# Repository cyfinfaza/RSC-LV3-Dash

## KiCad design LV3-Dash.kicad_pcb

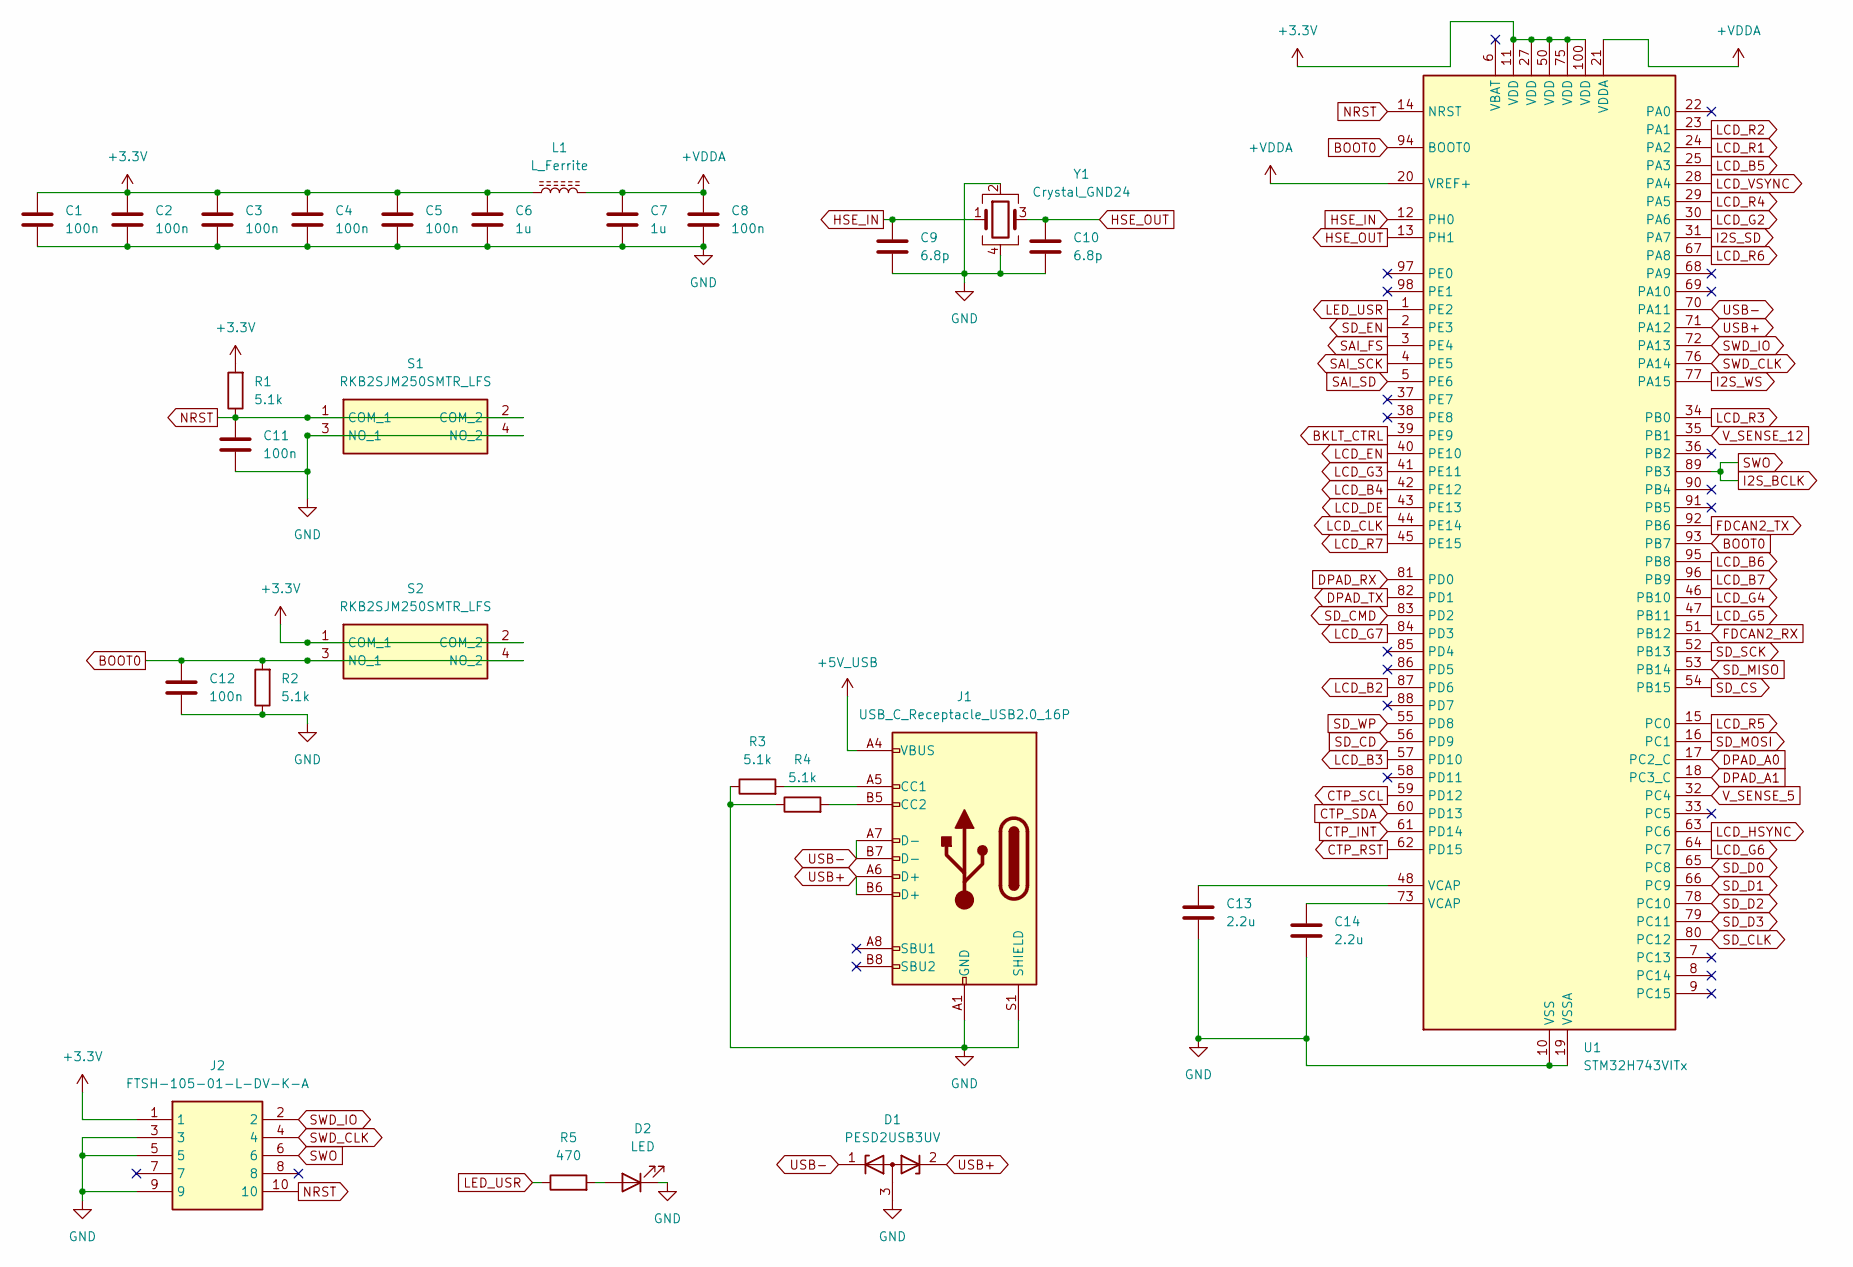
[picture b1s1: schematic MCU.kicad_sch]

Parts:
C1, C2, C3, C4, C5, C8, C11, C12: 100n; C_0603_1608Metric_Pad1.08x0.95mm_HandSolder
C6, C7: 1u; C_0603_1608Metric_Pad1.08x0.95mm_HandSolder
C9, C10: 6.8p; C_0603_1608Metric_Pad1.08x0.95mm_HandSolder
C13, C14: 2.2u; C_0603_1608Metric_Pad1.08x0.95mm_HandSolder
D1: PESD2USB3UV; SOT-23W
D2: LED; LED_0603_1608Metric_Pad1.05x0.95mm_HandSolder
J1: USB_C_Receptacle_USB2.0_16P; USB_C_Receptacle_HRO_TYPE-C-31-M-12
J2: FTSH-105-01-L-DV-K-A; FTSH-105-XX-YYY-DV-K-A; Mouser Part Number 200-FTSH10501LDVKA
L1: L_Ferrite; L_0603_1608Metric_Pad1.05x0.95mm_HandSolder
R1, R2, R3, R4: 5.1k; R_0603_1608Metric_Pad0.98x0.95mm_HandSolder
R5: 470; R_0603_1608Metric_Pad0.98x0.95mm_HandSolder
S1, S2: RKB2SJM250SMTR_LFS; RKB2SJM250SMTRLFS; Mouser Part Number 611-RKB2SJM250SMTRLF
U1: STM32H743VITx; LQFP-100_14x14mm_P0.5mm
Y1: Crystal_GND24; Crystal_SMD_3225-4Pin_3.2x2.5mm

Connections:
+3.3V: C1.1, C2.1, C3.1, C4.1, C5.1, C6.1, J2.1, L1.1, R1.2, S2.1 (COM_1), S2.2 (COM_2), U1.11 (VDD), U1.27 (VDD), U1.50 (VDD), U1.75 (VDD), U1.100 (VDD); also elsewhere on the board
+5V_USB: J1.A4 (VBUS), J1.A9 (VBUS), J1.B4 (VBUS), J1.B9 (VBUS); also elsewhere on the board
+VDDA: C7.1, C8.1, L1.2, U1.20 (VREF+), U1.21 (VDDA)
BKLT_CTRL: U1.39 (PE9); also elsewhere on the board
BOOT0: C12.1, R2.2, S2.3 (NO_1), S2.4 (NO_2), U1.93 (PB7), U1.94 (BOOT0)
CTP_INT: U1.61 (PD14); also elsewhere on the board
CTP_RST: U1.62 (PD15); also elsewhere on the board
CTP_SCL: U1.59 (PD12); also elsewhere on the board
CTP_SDA: U1.60 (PD13); also elsewhere on the board
DPAD_A0: U1.17 (PC2_C), U1.82 (PD1); also elsewhere on the board
DPAD_A1: U1.18 (PC3_C), U1.81 (PD0); also elsewhere on the board
FDCAN2_RX: U1.51 (PB12); also elsewhere on the board
FDCAN2_TX: U1.92 (PB6); also elsewhere on the board
GND: C1.2, C2.2, C3.2, C4.2, C5.2, C6.2, C7.2, C8.2, C9.2, C10.2, C11.2, C12.2, C13.2, C14.2, D1.3 (A), D2.1 (K), J1.A1 (GND), J1.A12 (GND), J1.B1 (GND), J1.B12 (GND), J1.S1 (SHIELD), J2.3, J2.5, J2.9, R2.1, R3.1, R4.1, S1.3 (NO_1), S1.4 (NO_2), U1.10 (VSS), U1.19 (VSSA), U1.26 (VSS), U1.49 (VSS), U1.74 (VSS), U1.99 (VSS), Y1.2, Y1.4; also elsewhere on the board
HSE_IN: C9.1, U1.12 (PH0), Y1.1
HSE_OUT: C10.1, U1.13 (PH1), Y1.3
I2S_BCLK: J2.6, U1.89 (PB3); also elsewhere on the board
I2S_SD: U1.31 (PA7); also elsewhere on the board
I2S_WS: U1.77 (PA15); also elsewhere on the board
LCD_B2: U1.87 (PD6); also elsewhere on the board
LCD_B3: U1.57 (PD10); also elsewhere on the board
LCD_B4: U1.42 (PE12); also elsewhere on the board
LCD_B5: U1.25 (PA3); also elsewhere on the board
LCD_B6: U1.95 (PB8); also elsewhere on the board
LCD_B7: U1.96 (PB9); also elsewhere on the board
LCD_CLK: U1.44 (PE14); also elsewhere on the board
LCD_DE: U1.43 (PE13); also elsewhere on the board
LCD_EN: U1.40 (PE10); also elsewhere on the board
LCD_G2: U1.30 (PA6); also elsewhere on the board
LCD_G3: U1.41 (PE11); also elsewhere on the board
LCD_G4: U1.46 (PB10); also elsewhere on the board
LCD_G5: U1.47 (PB11); also elsewhere on the board
LCD_G6: U1.64 (PC7); also elsewhere on the board
LCD_G7: U1.84 (PD3); also elsewhere on the board
LCD_HSYNC: U1.63 (PC6); also elsewhere on the board
LCD_R1: U1.24 (PA2)
LCD_R2: U1.23 (PA1); also elsewhere on the board
LCD_R3: U1.34 (PB0); also elsewhere on the board
LCD_R4: U1.29 (PA5); also elsewhere on the board
LCD_R5: U1.15 (PC0); also elsewhere on the board
LCD_R6: U1.67 (PA8); also elsewhere on the board
LCD_R7: U1.45 (PE15); also elsewhere on the board
LCD_VSYNC: U1.28 (PA4); also elsewhere on the board
LED_USR: R5.1, U1.1 (PE2)
NRST: C11.1, J2.10, R1.1, S1.1 (COM_1), S1.2 (COM_2), U1.14 (NRST)
unnamed: C13.1, U1.48 (VCAP)
unnamed: C14.1, U1.73 (VCAP)
unnamed: D2.2 (A), R5.2
unnamed: J1.A5 (CC1), R3.2
unnamed: J1.B5 (CC2), R4.2
SAI_FS: U1.3 (PE4); also elsewhere on the board
SAI_SCK: U1.4 (PE5); also elsewhere on the board
SAI_SD: U1.5 (PE6); also elsewhere on the board
SD_CD: U1.56 (PD9); also elsewhere on the board
SD_CLK: U1.52 (PB13), U1.80 (PC12); also elsewhere on the board
SD_CMD: U1.16 (PC1), U1.83 (PD2); also elsewhere on the board
SD_CS: U1.54 (PB15), U1.79 (PC11); also elsewhere on the board
SD_D0: U1.53 (PB14), U1.65 (PC8); also elsewhere on the board
SD_D1: U1.66 (PC9); also elsewhere on the board
SD_D2: U1.78 (PC10); also elsewhere on the board
SD_EN: U1.2 (PE3); also elsewhere on the board
SD_WP: U1.55 (PD8); also elsewhere on the board
SWD_CLK: J2.4, U1.76 (PA14)
SWD_IO: J2.2, U1.72 (PA13)
USB+: D1.2 (K), J1.A6 (D+), J1.B6 (D+), U1.71 (PA12)
USB-: D1.1 (K), J1.A7 (D-), J1.B7 (D-), U1.70 (PA11)
V_SENSE_5: U1.32 (PC4); also elsewhere on the board
V_SENSE_12: U1.35 (PB1); also elsewhere on the board

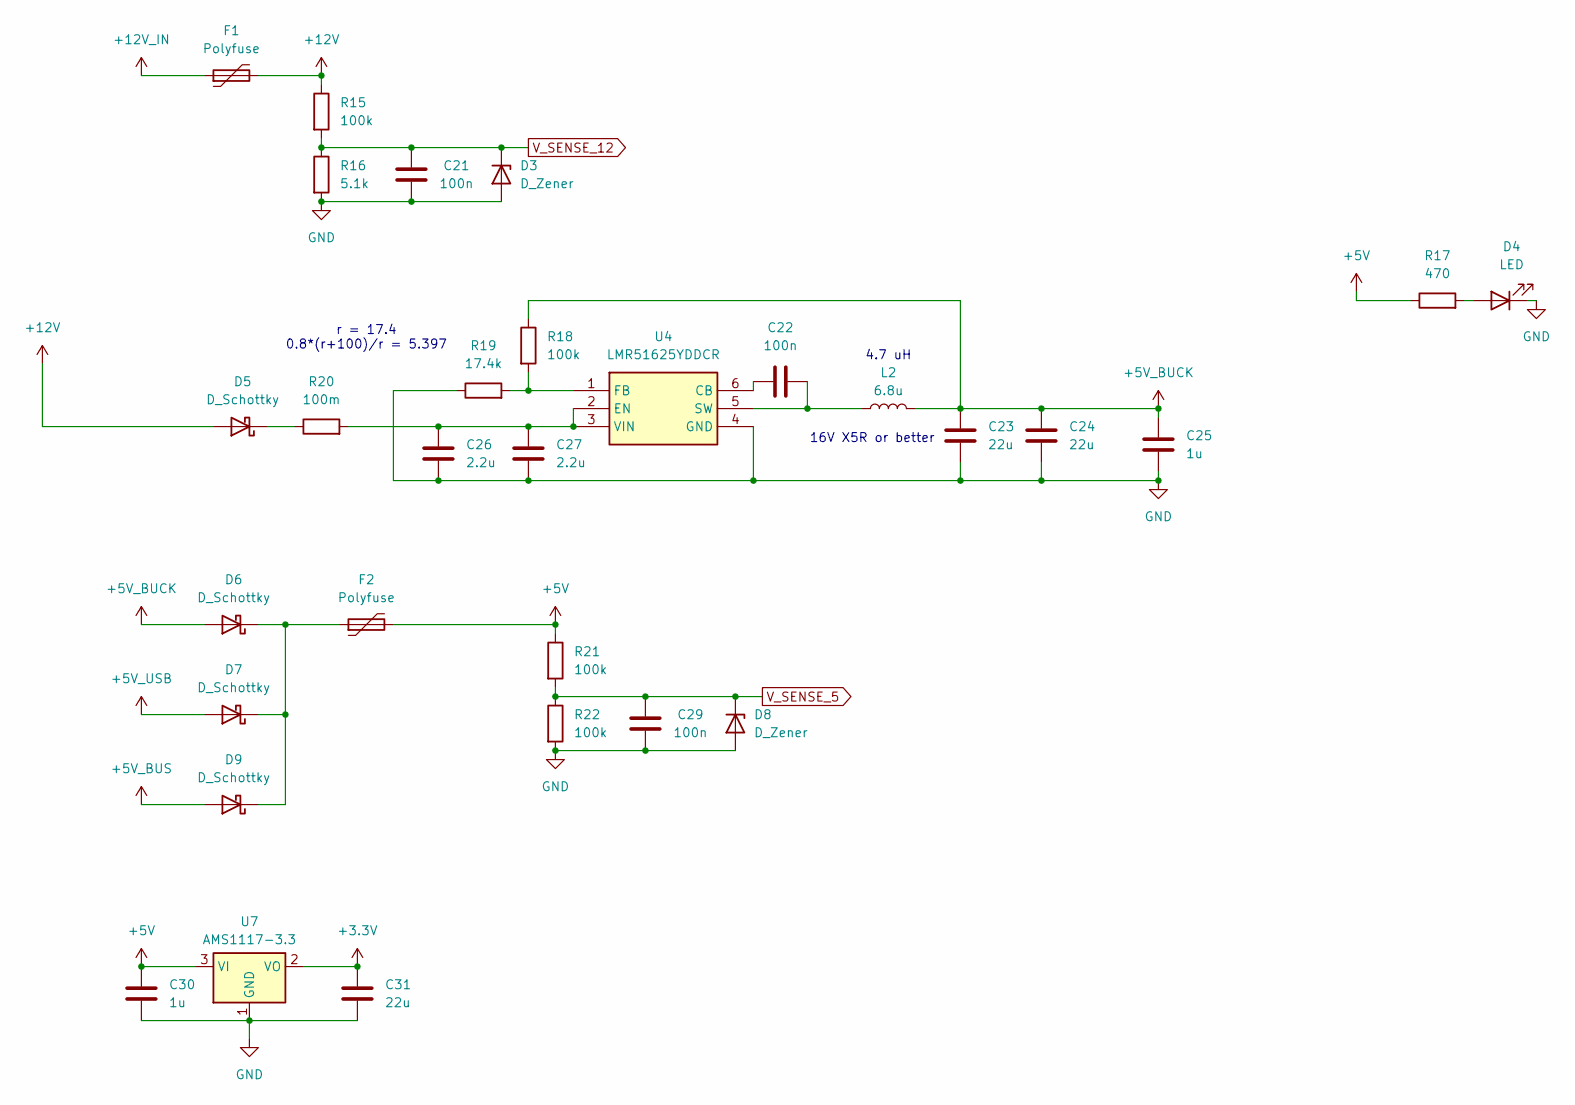
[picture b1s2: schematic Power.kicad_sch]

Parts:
C21, C22, C29: 100n; C_0603_1608Metric_Pad1.08x0.95mm_HandSolder
C23, C24, C31: 22u; C_1206_3216Metric_Pad1.33x1.80mm_HandSolder
C25, C30: 1u; C_0603_1608Metric_Pad1.08x0.95mm_HandSolder
C26, C27: 2.2u; C_0603_1608Metric_Pad1.08x0.95mm_HandSolder
D3, D8: D_Zener; D_SOD-323_HandSoldering
D4: LED; LED_0603_1608Metric_Pad1.05x0.95mm_HandSolder
D5, D6, D7, D9: D_Schottky; D_SOD-123F
F1, F2: Polyfuse; Fuse_1812_4532Metric_Pad1.30x3.40mm_HandSolder
L2: 6.8u; L_Bourns-SRN4018
R15, R18, R21, R22: 100k; R_0603_1608Metric_Pad0.98x0.95mm_HandSolder
R16: 5.1k; R_0603_1608Metric_Pad0.98x0.95mm_HandSolder
R17: 470; R_0603_1608Metric_Pad0.98x0.95mm_HandSolder
R19: 17.4k; R_0603_1608Metric_Pad0.98x0.95mm_HandSolder
R20: 100m; R_1206_3216Metric_Pad1.30x1.75mm_HandSolder
U4: LMR51625YDDCR; SOT95P280X110-6N; Manufacturer_Part_Number LMR51625YFDDCR; Mouser Part Number 595-LMR51625YFDDCR
U7: AMS1117-3.3; SOT-223-3_TabPin2

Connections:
+3.3V: C31.1, U7.2 (VO); also elsewhere on the board
+5V: C30.1, F2.2, R17.1, R21.1, U7.3 (VI); also elsewhere on the board
+5V_BUCK: C23.1, C24.1, C25.1, D6.2 (A), L2.2, R18.1
+5V_BUS: D9.2 (A); also elsewhere on the board
+5V_USB: D7.2 (A); also elsewhere on the board
+12V: D5.2 (A), F1.2, R15.1
+12V_IN: F1.1; also elsewhere on the board
GND: C21.2, C23.2, C24.2, C25.2, C26.2, C27.2, C29.2, C30.2, C31.2, D3.2 (A), D4.1 (K), D8.2 (A), R16.2, R19.1, R22.2, U4.4 (GND), U7.1 (GND); also elsewhere on the board
unnamed: D4.2 (A), R17.2
unnamed: D5.1 (K), R20.1
unnamed: D6.1 (K), D7.1 (K), D9.1 (K), F2.1
unnamed: C22.1, U4.6 (CB)
unnamed: C26.1, C27.1, R20.2, U4.2 (EN), U4.3 (VIN)
unnamed: R18.2, R19.2, U4.1 (FB)
unnamed: C22.2, L2.1, U4.5 (SW)
V_SENSE_5: C29.1, D8.1 (K), R21.2, R22.1; also elsewhere on the board
V_SENSE_12: C21.1, D3.1 (K), R15.2, R16.1; also elsewhere on the board

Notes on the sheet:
16V X5R or better
4.7 uH
r = 17.4 0.8*(r+100)/r = 5.397

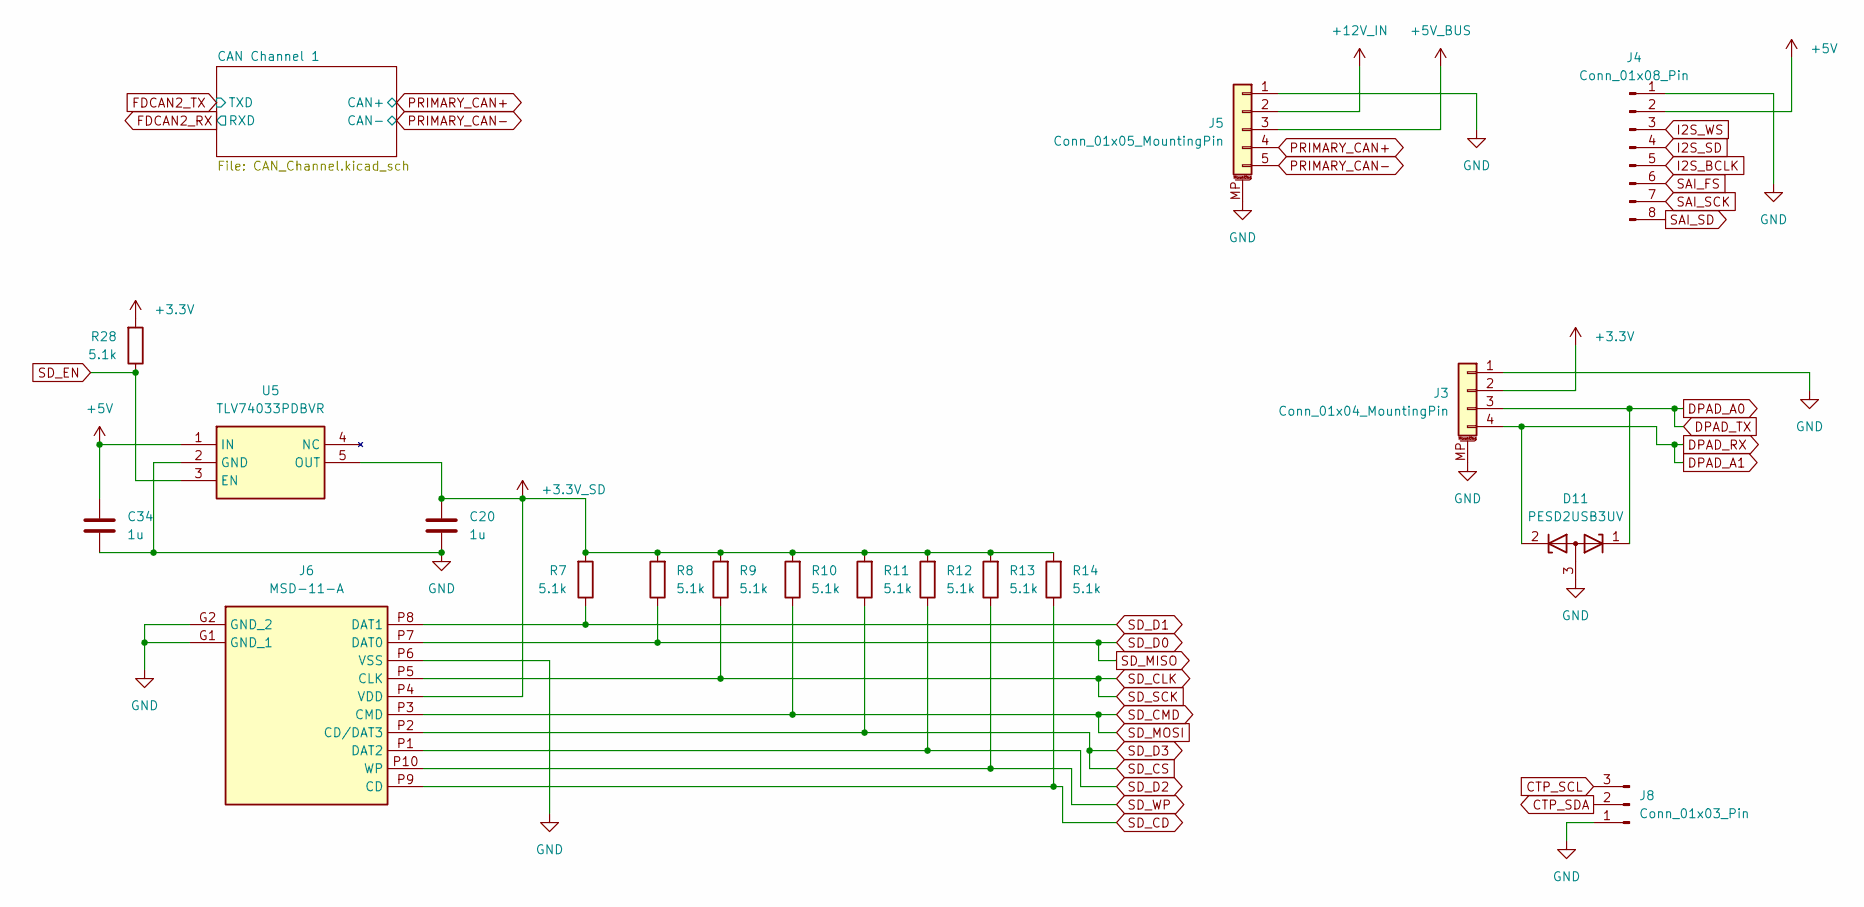
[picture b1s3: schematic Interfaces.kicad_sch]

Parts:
C20, C34: 1u; C_0603_1608Metric_Pad1.08x0.95mm_HandSolder
D11: PESD2USB3UV; SOT-23W
J3: Conn_01x04_MountingPin; Molex_Micro-Fit_3.0_43650-0410_1x04-1MP_P3.00mm_Horizontal
J4: Conn_01x08_Pin; PinHeader_1x08_P2.54mm_Vertical
J5: Conn_01x05_MountingPin; Molex_Micro-Fit_3.0_43650-0510_1x05-1MP_P3.00mm_Horizontal
J6: MSD-11-A; MSD11A; Mouser Part Number 179-MSD-11-A
J8: Conn_01x03_Pin; PinHeader_1x03_P2.54mm_Vertical
R7, R8, R9, R10, R11, R12, R13, R14, R28: 5.1k; R_0603_1608Metric_Pad0.98x0.95mm_HandSolder
U5: TLV74033PDBVR; SOT95P280X145-5N; Mouser Part Number 595-TLV74033PDBVR

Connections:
+3.3V: J3.2, R28.2; also elsewhere on the board
+3.3V_SD: C20.1, J6.P4 (VDD), R7.2, R8.2, R9.2, R10.2, R11.2, R12.2, R13.2, R14.2, U5.5 (OUT)
+5V: C34.1, J4.2, U5.1 (IN); also elsewhere on the board
+5V_BUS: J5.3; also elsewhere on the board
+12V_IN: J5.2; also elsewhere on the board
CTP_SCL: J8.3; also elsewhere on the board
CTP_SDA: J8.2; also elsewhere on the board
DPAD_A0: D11.1 (K), J3.3; also elsewhere on the board
DPAD_A1: D11.2 (K), J3.4; also elsewhere on the board
GND: C20.2, C34.2, D11.3 (A), J3.1, J3.MP (MountPin), J4.1, J5.1, J5.MP (MountPin), J6.G1 (GND_1), J6.G2 (GND_2), J6.P6 (VSS), J8.1, U5.2 (GND); also elsewhere on the board
I2S_BCLK: J4.5; also elsewhere on the board
I2S_SD: J4.4; also elsewhere on the board
I2S_WS: J4.3; also elsewhere on the board
PRIMARY_CAN+: J5.4; also elsewhere on the board
PRIMARY_CAN-: J5.5; also elsewhere on the board
SAI_FS: J4.6; also elsewhere on the board
SAI_SCK: J4.7; also elsewhere on the board
SAI_SD: J4.8; also elsewhere on the board
SD_CD: J6.P9 (CD), R14.1; also elsewhere on the board
SD_CLK: J6.P5 (CLK), R9.1; also elsewhere on the board
SD_CMD: J6.P3 (CMD), R10.1; also elsewhere on the board
SD_CS: J6.P2 (CD/DAT3), R11.1; also elsewhere on the board
SD_D0: J6.P7 (DAT0), R8.1; also elsewhere on the board
SD_D1: J6.P8 (DAT1), R7.1; also elsewhere on the board
SD_D2: J6.P1 (DAT2), R12.1; also elsewhere on the board
SD_EN: R28.1, U5.3 (EN); also elsewhere on the board
SD_WP: J6.P10 (WP), R13.1; also elsewhere on the board

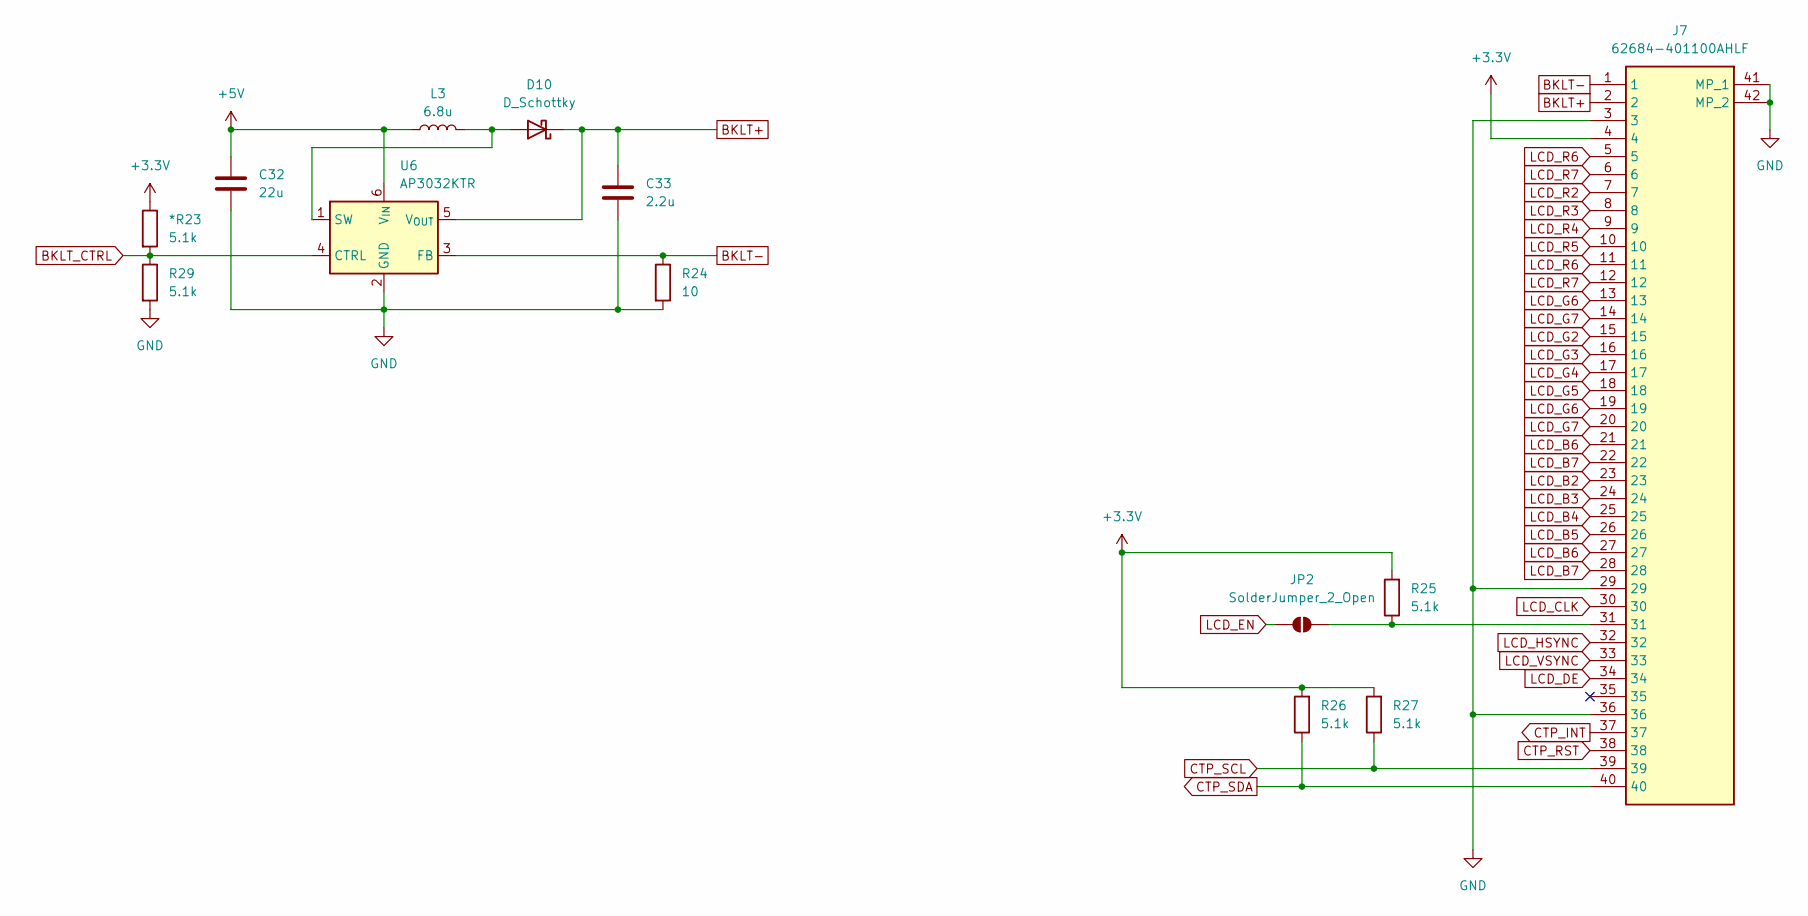
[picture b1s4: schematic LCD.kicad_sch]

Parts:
*R23: 5.1k; R_0603_1608Metric_Pad0.98x0.95mm_HandSolder
C32: 22u; C_1206_3216Metric_Pad1.33x1.80mm_HandSolder
C33: 2.2u; C_0603_1608Metric_Pad1.08x0.95mm_HandSolder
D10: D_Schottky; D_SOD-123F
J7: 62684-401100AHLF; 62684401100AHLF; Mouser Part Number 649-62684-401100AHLF
JP2: SolderJumper_2_Open; SolderJumper-2_P1.3mm_Open_RoundedPad1.0x1.5mm
L3: 6.8u; L_Bourns-SRN4018
R24: 10; R_0603_1608Metric_Pad0.98x0.95mm_HandSolder
R25, R26, R27, R29: 5.1k; R_0603_1608Metric_Pad0.98x0.95mm_HandSolder
U6: AP3032KTR; SOT-23-6

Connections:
+3.3V: *R23.1, J7.4, R25.2, R26.2, R27.2; also elsewhere on the board
+5V: C32.1, L3.1, U6.6 (V_{IN}); also elsewhere on the board
BKLT+: C33.1, D10.1 (K), J7.2, U6.5 (V_{OUT})
BKLT-: J7.1, R24.1, U6.3 (FB)
BKLT_CTRL: *R23.2, R29.1, U6.4 (CTRL); also elsewhere on the board
CTP_INT: J7.37; also elsewhere on the board
CTP_RST: J7.38; also elsewhere on the board
CTP_SCL: J7.39, R27.1; also elsewhere on the board
CTP_SDA: J7.40, R26.1; also elsewhere on the board
GND: C32.2, C33.2, J7.3, J7.29, J7.36, J7.41 (MP_1), J7.42 (MP_2), R24.2, R29.2, U6.2 (GND); also elsewhere on the board
LCD_B2: J7.23; also elsewhere on the board
LCD_B3: J7.24; also elsewhere on the board
LCD_B4: J7.25; also elsewhere on the board
LCD_B5: J7.26; also elsewhere on the board
LCD_B6: J7.21, J7.27; also elsewhere on the board
LCD_B7: J7.22, J7.28; also elsewhere on the board
LCD_CLK: J7.30; also elsewhere on the board
LCD_DE: J7.34; also elsewhere on the board
LCD_EN: JP2.1 (A); also elsewhere on the board
LCD_G2: J7.15; also elsewhere on the board
LCD_G3: J7.16; also elsewhere on the board
LCD_G4: J7.17; also elsewhere on the board
LCD_G5: J7.18; also elsewhere on the board
LCD_G6: J7.13, J7.19; also elsewhere on the board
LCD_G7: J7.14, J7.20; also elsewhere on the board
LCD_HSYNC: J7.32; also elsewhere on the board
LCD_R2: J7.7; also elsewhere on the board
LCD_R3: J7.8; also elsewhere on the board
LCD_R4: J7.9; also elsewhere on the board
LCD_R5: J7.10; also elsewhere on the board
LCD_R6: J7.5, J7.11; also elsewhere on the board
LCD_R7: J7.6, J7.12; also elsewhere on the board
LCD_VSYNC: J7.33; also elsewhere on the board
unnamed: D10.2 (A), L3.2, U6.1 (SW)
unnamed: J7.31, JP2.2 (B), R25.1

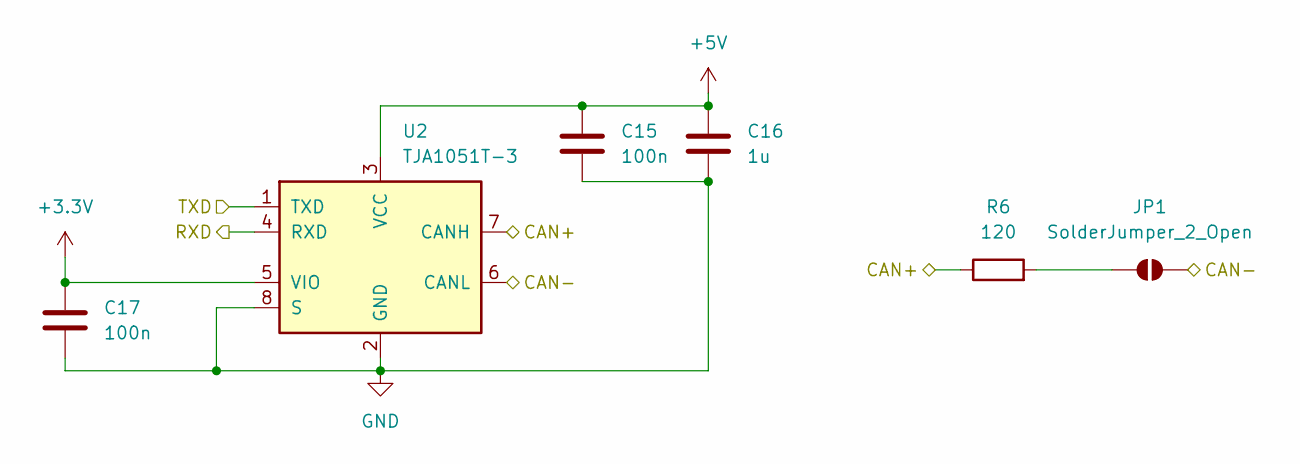
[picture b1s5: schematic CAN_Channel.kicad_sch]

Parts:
C15, C17: 100n; C_0603_1608Metric_Pad1.08x0.95mm_HandSolder
C16: 1u; C_0603_1608Metric_Pad1.08x0.95mm_HandSolder
JP1: SolderJumper_2_Open; SolderJumper-2_P1.3mm_Open_RoundedPad1.0x1.5mm
R6: 120; R_0603_1608Metric_Pad0.98x0.95mm_HandSolder
U2: TJA1051T-3; SOIC-8_3.9x4.9mm_P1.27mm

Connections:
+3.3V: C17.1, U2.5 (VIO); also elsewhere on the board
+5V: C15.1, C16.1, U2.3 (VCC); also elsewhere on the board
FDCAN2_RX: U2.4 (RXD); also elsewhere on the board
FDCAN2_TX: U2.1 (TXD); also elsewhere on the board
GND: C15.2, C16.2, C17.2, U2.2 (GND), U2.8 (S); also elsewhere on the board
unnamed: JP1.1 (A), R6.2
PRIMARY_CAN+: R6.1, U2.7 (CANH); also elsewhere on the board
PRIMARY_CAN-: JP1.2 (B), U2.6 (CANL); also elsewhere on the board

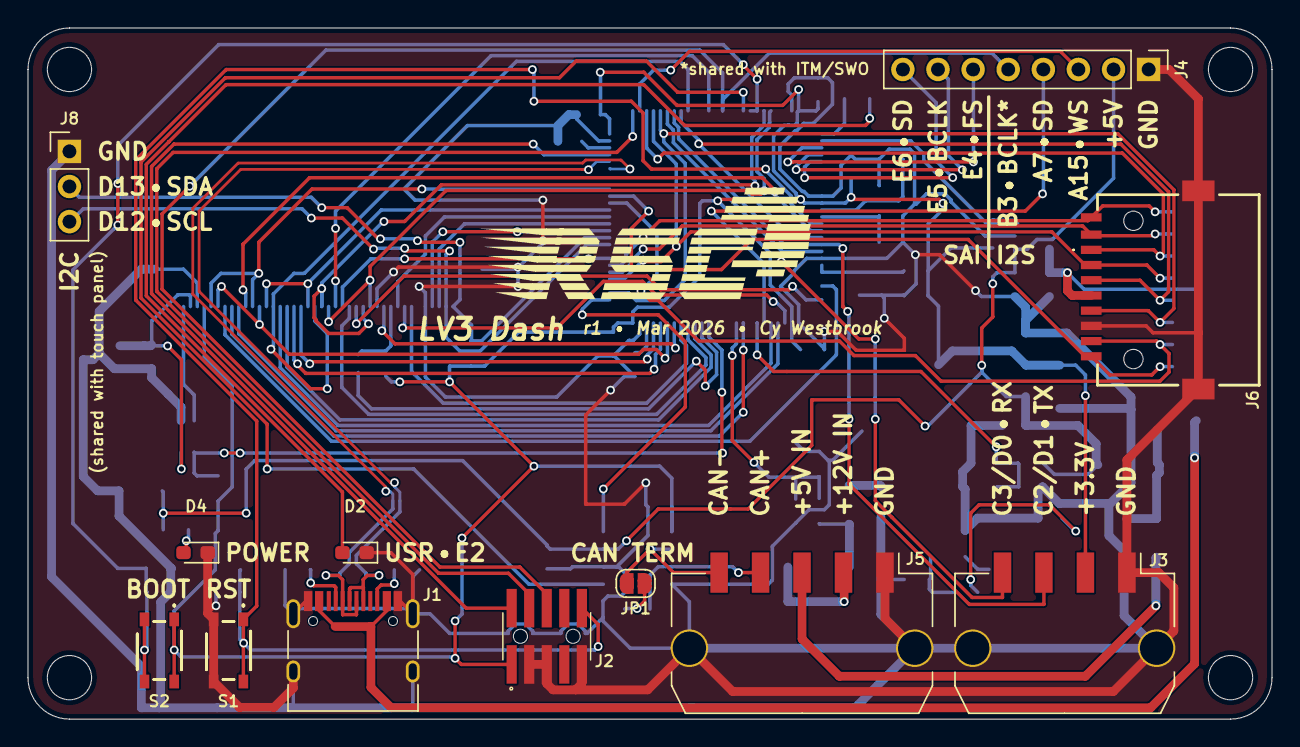
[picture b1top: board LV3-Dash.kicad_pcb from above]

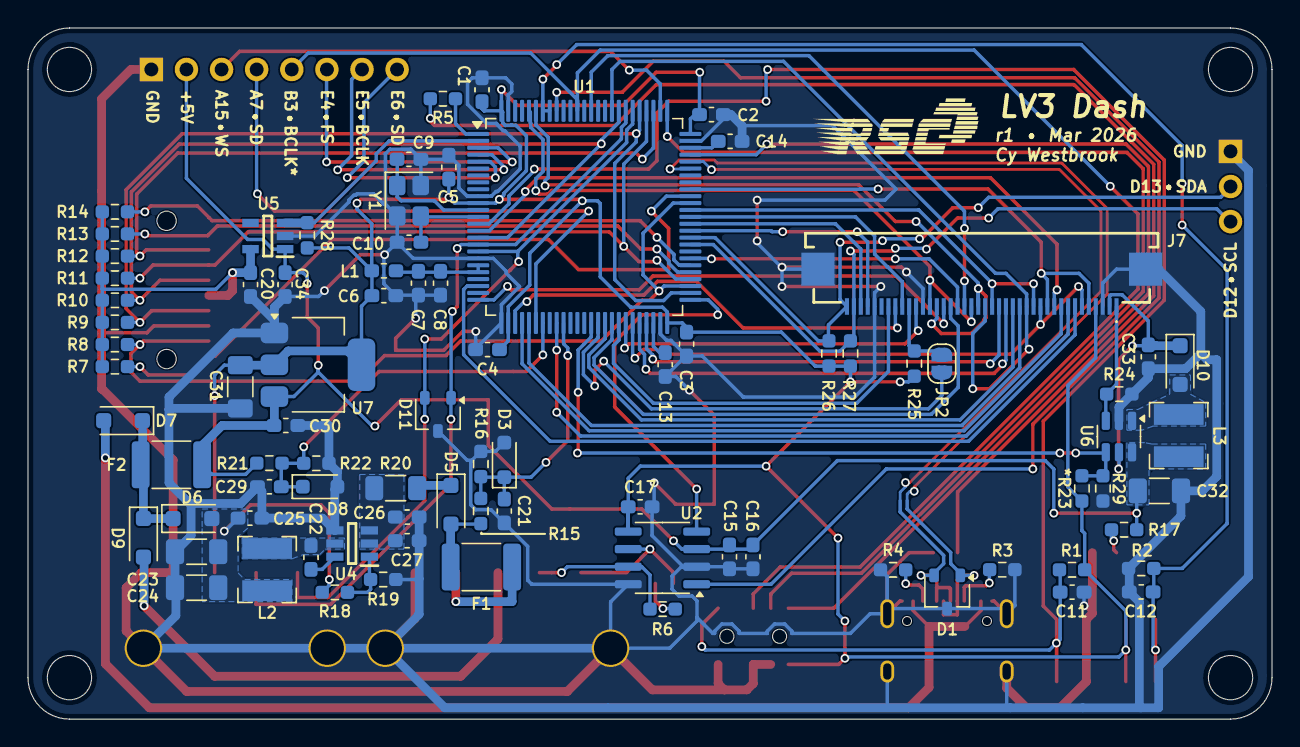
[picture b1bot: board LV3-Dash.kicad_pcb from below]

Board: 2 copper layers, 90.0 x 50.0 mm, 95 parts (83 on the bottom side), 87 nets.

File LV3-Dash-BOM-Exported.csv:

"Reference","Qty","Value","DNP","Exclude from BOM","Exclude from Board","Footprint","Datasheet"
"R1,R2,R3,R4,R7,R8,R9,R10,R11,R12,R13,R14,R16,R23,R25,R26,R27,R28","18","5.1k","","","","Resistor_SMD:R_0603_1608Metric_Pad0.98x0.95mm_HandSolder","~"
"C1,C2,C3,C4,C5,C8,C11,C12,C15,C17,C21,C22,C29","13","100n","","","","Capacitor_SMD:C_0603_1608Metric_Pad1.08x0.95mm_HandSolder","~"
"C6,C7,C16,C20,C25,C30,C34","7","1u","","","","Capacitor_SMD:C_0603_1608Metric_Pad1.08x0.95mm_HandSolder","~"
"D5,D6,D7,D9,D10","5","D_Schottky","","","","Diode_SMD:D_SOD-123F","~"
"C13,C14,C26,C27,C33","5","2.2u","","","","Capacitor_SMD:C_0603_1608Metric_Pad1.08x0.95mm_HandSolder","~"
"R15,R18,R21,R22","4","100k","","","","Resistor_SMD:R_0603_1608Metric_Pad0.98x0.95mm_HandSolder","~"
"C23,C24,C31,C32","4","22u","","","","Capacitor_SMD:C_1206_3216Metric_Pad1.33x1.80mm_HandSolder","~"
"S1,S2","2","RKB2SJM250SMTR_LFS","","","","RKB2SJM250SMTRLFS","https://www.ckswitches.com/media/3130/ck_rk_datasheet.pdf"
"R5,R17","2","470","","","","Resistor_SMD:R_0603_1608Metric_Pad0.98x0.95mm_HandSolder","~"
"L2,L3","2","6.8u","","","","Inductor_SMD:L_Bourns-SRN4018","~"
"JP1,JP2","2","SolderJumper_2_Open","","Excluded from BOM","","Jumper:SolderJumper-2_P1.3mm_Open_RoundedPad1.0x1.5mm","~"
"F1,F2","2","Polyfuse","","","","Fuse:Fuse_1812_4532Metric_Pad1.30x3.40mm_HandSolder","~"
"D3,D8","2","D_Zener","","","","Diode_SMD:D_SOD-323_HandSoldering","~"
"D2,D4","2","LED","","","","LED_SMD:LED_0603_1608Metric_Pad1.05x0.95mm_HandSolder","~"
"D1,D11","2","PESD2USB3UV","","","","Package_TO_SOT_SMD:SOT-23W","~"
"C9,C10","2","6.8p","","","","Capacitor_SMD:C_0603_1608Metric_Pad1.08x0.95mm_HandSolder","~"
"Y1","1","Crystal_GND24","","","","Crystal:Crystal_SMD_3225-4Pin_3.2x2.5mm","~"
"U7","1","AMS1117-3.3","","","","Package_TO_SOT_SMD:SOT-223-3_TabPin2","http://www.advanced-monolithic.com/pdf/ds1117.pdf"
"U6","1","AP3032KTR","","","","Package_TO_SOT_SMD:SOT-23-6","https://www.diodes.com/assets/Datasheets/AP3019A.pdf"
"U5","1","TLV74033PDBVR","","","","SamacSys_Parts:SOT95P280X145-5N","https://www.ti.com/lit/ds/symlink/tlv740p.pdf?ts=15996478844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"
"U4","1","LMR51625YDDCR","","","","SamacSys_Parts:SOT95P280X110-6N","https://www.mouser.kr/ProductDetail/Texas-Instruments/LMR516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"
"U2","1","TJA1051T-3","","","","Package_SO:SOIC-8_3.9x4.9mm_P1.27mm","http://www.nxp.com/docs/en/data-sheet/TJA1051.pdf"
"U1","1","STM32H743VITx","","","","Package_QFP:LQFP-100_14x14mm_P0.5mm","https://www.st.com/resource/en/datasheet/stm32h743vi.pdf"
"R24","1","10","","","","Resistor_SMD:R_0603_1608Metric_Pad0.98x0.95mm_HandSolder","~"
"R20","1","100m","","","","Resistor_SMD:R_1206_3216Metric_Pad1.30x1.75mm_HandSolder","~"
"R19","1","17.4k","","","","Resistor_SMD:R_0603_1608Metric_Pad0.98x0.95mm_HandSolder","~"
"R6","1","120","","","","Resistor_SMD:R_0603_1608Metric_Pad0.98x0.95mm_HandSolder","~"
"L1","1","L_Ferrite","","","","Inductor_SMD:L_0603_1608Metric_Pad1.05x0.95mm_HandSolder","~"
"J7","1","62684-401100AHLF","","","","62684401100AHLF","https://cdn.amphenol-cs.com/media/wysiwyg/files/drawing/62684.pdf"
"J6","1","MSD-11-A","","","","SamacSys_Parts:MSD11A","https://www.sameskydevices.com/product/resource/msd-11-a.pdf"
"J5","1","Conn_01x05_MountingPin","","","","Connector_Molex:Molex_Micro-Fit_3.0_43650-0510_1x05-1MP_P3.00mm_Horizontal","~"
"J4","1","Conn_01x05_Pin","","","","Connector_PinHeader_2.54mm:PinHeader_1x05_P2.54mm_Vertical","~"
"J3","1","Conn_01x04_MountingPin","","","","Connector_Molex:Molex_Micro-Fit_3.0_43650-0410_1x04-1MP_P3.00mm_Horizontal","~"
"J2","1","FTSH-105-01-L-DV-K-A","","","","SamacSys_Parts:FTSH-105-XX-YYY-DV-K-A","http://suddendocs.samtec.com/prints/ftsh-1xx-xx-xxx-dv-xxx-x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"
"J1","1","USB_C_Receptacle_USB2.0_16P","","","","Connector_USB:USB_C_Receptacle_HRO_TYPE-C-31-M-12","https://www.usb.org/sites/default/files/documents/usb_type-c.zip"

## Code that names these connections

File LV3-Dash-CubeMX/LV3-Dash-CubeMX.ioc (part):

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Mcu.Name=STM32H743VITx
Mcu.Package=LQFP100
Mcu.UserName=STM32H743VITx
PA1.Mode=RGB666
PA1.Signal=LTDC_R2
PA11.Mode=Host_Only
PA11.Signal=USB_OTG_FS_DM
PA12.Mode=Host_Only
PA12.Signal=USB_OTG_FS_DP
PA13\ (JTMS/SWDIO).Mode=Serial_Wire
PA13\ (JTMS/SWDIO).Signal=DEBUG_JTMS-SWDIO
PA14\ (JTCK/SWCLK).Mode=Serial_Wire
PA14\ (JTCK/SWCLK).Signal=DEBUG_JTCK-SWCLK
PA15\ (JTDI).Mode=Half_Duplex_Master_Tx
PA15\ (JTDI).Signal=I2S1_WS
PA2.Mode=RGB666
PA2.Signal=LTDC_R1
PA3.Mode=RGB666
PA3.Signal=LTDC_B5
PA4.Mode=RGB666
PA4.Signal=LTDC_VSYNC
PA5.Mode=RGB666
PA5.Signal=LTDC_R4
PA6.Mode=RGB666
PA6.Signal=LTDC_G2
PA7.Mode=Half_Duplex_Master_Tx
PA7.Signal=I2S1_SDO
PA8.Mode=RGB666
PA8.Signal=LTDC_R6
PB0.Mode=RGB666
PB0.Signal=LTDC_R3
PB1.GPIOParameters=GPIO_Label
PB1.GPIO_Label=V_SENSE_12
PB1.Signal=ADCx_INP5
PB10.Mode=RGB666
PB10.Signal=LTDC_G4
PB11.Mode=RGB666
PB11.Signal=LTDC_G5
PB12.Mode=FDCAN_Activate
PB12.Signal=FDCAN2_RX
PB13.Mode=Full_Duplex_Master
PB13.Signal=SPI2_SCK
PB14.Mode=Full_Duplex_Master
PB14.Signal=SPI2_MISO
PB15.GPIOParameters=GPIO_Label
PB15.GPIO_Label=SD_CS
PB15.Signal=GPIO_Output
PB3\ (JTDO/TRACESWO).Mode=Half_Duplex_Master_Tx
PB3\ (JTDO/TRACESWO).Signal=I2S1_CK
PB6.Mode=FDCAN_Activate
PB6.Signal=FDCAN2_TX
PB7.GPIOParameters=GPIO_Label
PB7.GPIO_Label=BOOT0_SENSE
PB7.Signal=GPIO_Input
PB8.Mode=RGB666
PB8.Signal=LTDC_B6
PB9.Mode=RGB666
PB9.Signal=LTDC_B7
PC0.Mode=RGB666
PC0.Signal=LTDC_R5
PC1.Mode=Full_Duplex_Master
PC1.Signal=SPI2_MOSI
PC10.Mode=SD_4_bits_Wide_bus
PC10.Signal=SDMMC1_D2
PC11.Mode=SD_4_bits_Wide_bus
PC11.Signal=SDMMC1_D3
PC12.Mode=SD_4_bits_Wide_bus
PC12.Signal=SDMMC1_CK
PC2_C.GPIOParameters=GPIO_Label
PC2_C.GPIO_Label=DPAD_A0
PC2_C.Mode=IN0-Single-Ended
PC2_C.Signal=ADC3_INP0
PC3_C.GPIOParameters=GPIO_Label
PC3_C.GPIO_Label=DPAD_A1
PC3_C.Mode=IN1-Single-Ended
PC3_C.Signal=ADC3_INP1
PC4.GPIOParameters=GPIO_Label
PC4.GPIO_Label=V_SENSE_5
PC4.Signal=ADCx_INP4
PC6.Mode=RGB666
PC6.Signal=LTDC_HSYNC
PC7.Mode=RGB666
PC7.Signal=LTDC_G6
PC8.Mode=SD_4_bits_Wide_bus
PC8.Signal=SDMMC1_D0
PC9.Mode=SD_4_bits_Wide_bus
PC9.Signal=SDMMC1_D1
PD0.GPIOParameters=GPIO_Label
PD0.GPIO_Label=DPAD_RX
PD0.Mode=Asynchronous
PD0.Signal=UART4_RX
PD1.GPIOParameters=GPIO_Label
PD1.GPIO_Label=DPAD_TX
PD1.Mode=Asynchronous
PD1.Signal=UART4_TX
PD10.Mode=RGB666
PD10.Signal=LTDC_B3
PD12.GPIOParameters=GPIO_Label
PD12.GPIO_Label=CTP_SCL
PD12.Mode=I2C
PD12.Signal=I2C4_SCL
PD13.GPIOParameters=GPIO_Label
PD13.GPIO_Label=CTP_SDA
PD13.Mode=I2C
PD13.Signal=I2C4_SDA
PD14.GPIOParameters=GPIO_Label
PD14.GPIO_Label=CTP_INT
PD14.Signal=GPIO_Output
PD15.GPIOParameters=GPIO_Label
PD15.GPIO_Label=CTP_RST
PD15.Signal=GPIO_Output
PD2.Mode=SD_4_bits_Wide_bus
PD2.Signal=SDMMC1_CMD
PD3.Mode=RGB666
PD3.Signal=LTDC_G7
PD6.Mode=RGB666
PD6.Signal=LTDC_B2
PD8.GPIOParameters=GPIO_Label
PD8.GPIO_Label=SD_WP
PD8.Signal=GPIO_Output
PD9.GPIOParameters=GPIO_Label
PD9.GPIO_Label=SD_CD
PD9.Signal=GPIO_Output
PE10.GPIOParameters=GPIO_Label
PE10.GPIO_Label=LCD_EN
PE10.Signal=GPIO_Output
PE11.Mode=RGB666
PE11.Signal=LTDC_G3
PE12.Mode=RGB666
PE12.Signal=LTDC_B4
PE13.Mode=RGB666
PE13.Signal=LTDC_DE
PE14.Mode=RGB666
PE14.Signal=LTDC_CLK
PE15.Mode=RGB666
PE15.Signal=LTDC_R7
PE2.GPIOParameters=GPIO_Label
PE2.GPIO_Label=LED_USR
PE2.Signal=GPIO_Output
PE3.GPIOParameters=GPIO_Label
PE3.GPIO_Label=SD_EN
PE3.Signal=GPIO_Output
PE4.Mode=SAI_A_Master
PE4.Signal=SAI1_FS_A
PE5.Mode=SAI_A_Master
PE5.Signal=SAI1_SCK_A
PE6.Mode=SAI_A_Master
PE6.Signal=SAI1_SD_A
PE9.GPIOParameters=GPIO_Label
PE9.GPIO_Label=BKLT_CTRL
PE9.Signal=S_TIM1_CH1
PH0-OSC_IN\ (PH0).Mode=HSE-External-Oscillator
PH0-OSC_IN\ (PH0).Signal=RCC_OSC_IN
PH1-OSC_OUT\ (PH1).Mode=HSE-External-Oscillator
PH1-OSC_OUT\ (PH1).Signal=RCC_OSC_OUT
RCC.SYSCLKFreq_VALUE=64000000
board=custom

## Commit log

2025-11-29 LCD connector, backlight, other work
2025-12-22 preliminary complete schematic
2025-12-22 initial dimensions and placement
2025-12-23 fix swd connector orientation, modify 12v input
2025-12-23 basic layout organization, fix +VDDA typo
2025-12-24 full preliminary layout
2025-12-26 some preliminary routing
2025-12-27 finalize connector placement, modify layout
2025-12-28 3.3v regulator changes, GPIO output fixes, layout changes
2025-12-28 more preliminary routing, critical ground
2025-12-30 finalized schematic, some routing
2025-12-30 fix duplicate LCD_EN pin, initial ZIF routing
2025-12-30 initial routing of all signals, 5v 3.3v not done
2025-12-31 fully routed, needs cleanup, planes
2026-01-01 trace cleanup, ground planes, silkscreen cleanup
2026-01-04 fillets, graphics, other fixes
2026-01-11 FINAL FOR ORDER (4 Jan 2026)
2026-03-30 r1 final (see changelog.md)
